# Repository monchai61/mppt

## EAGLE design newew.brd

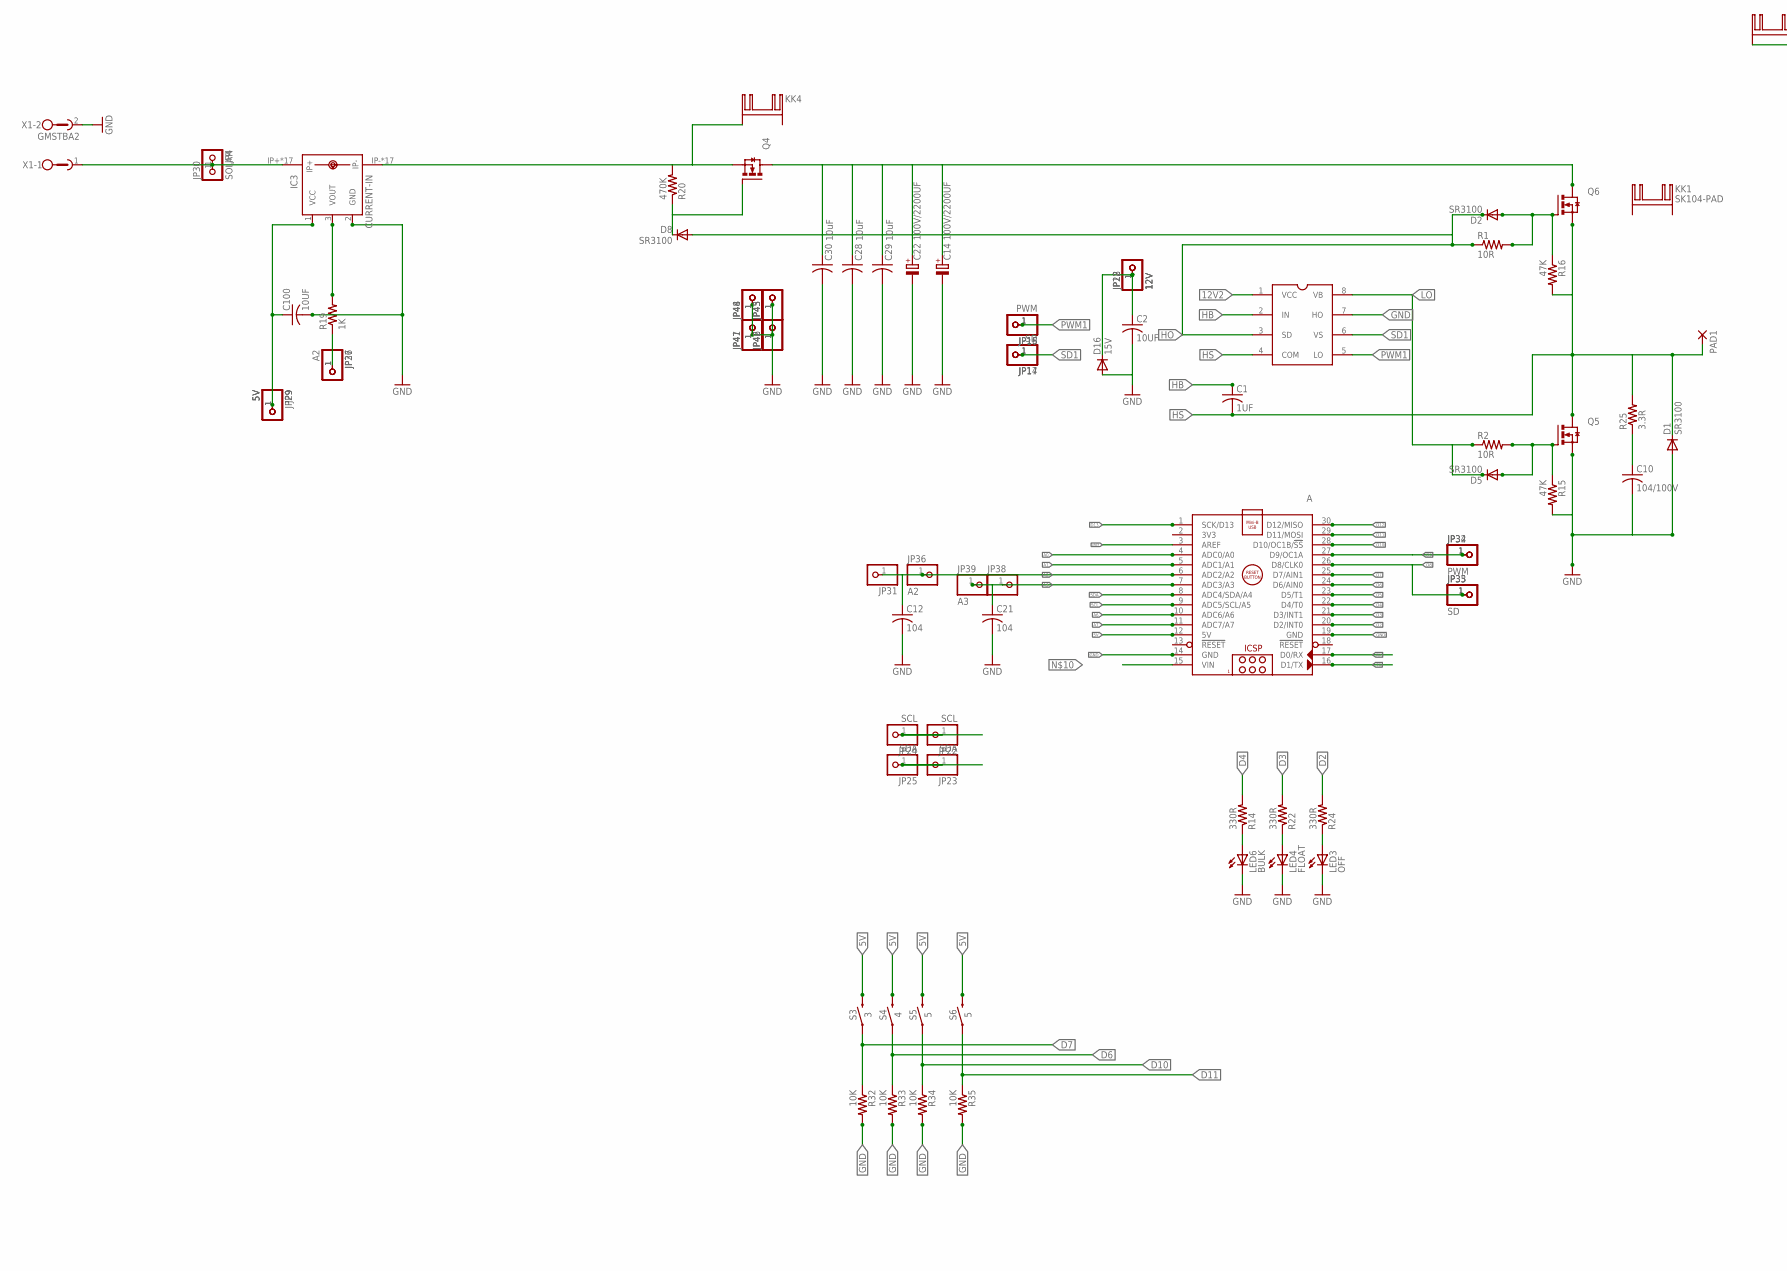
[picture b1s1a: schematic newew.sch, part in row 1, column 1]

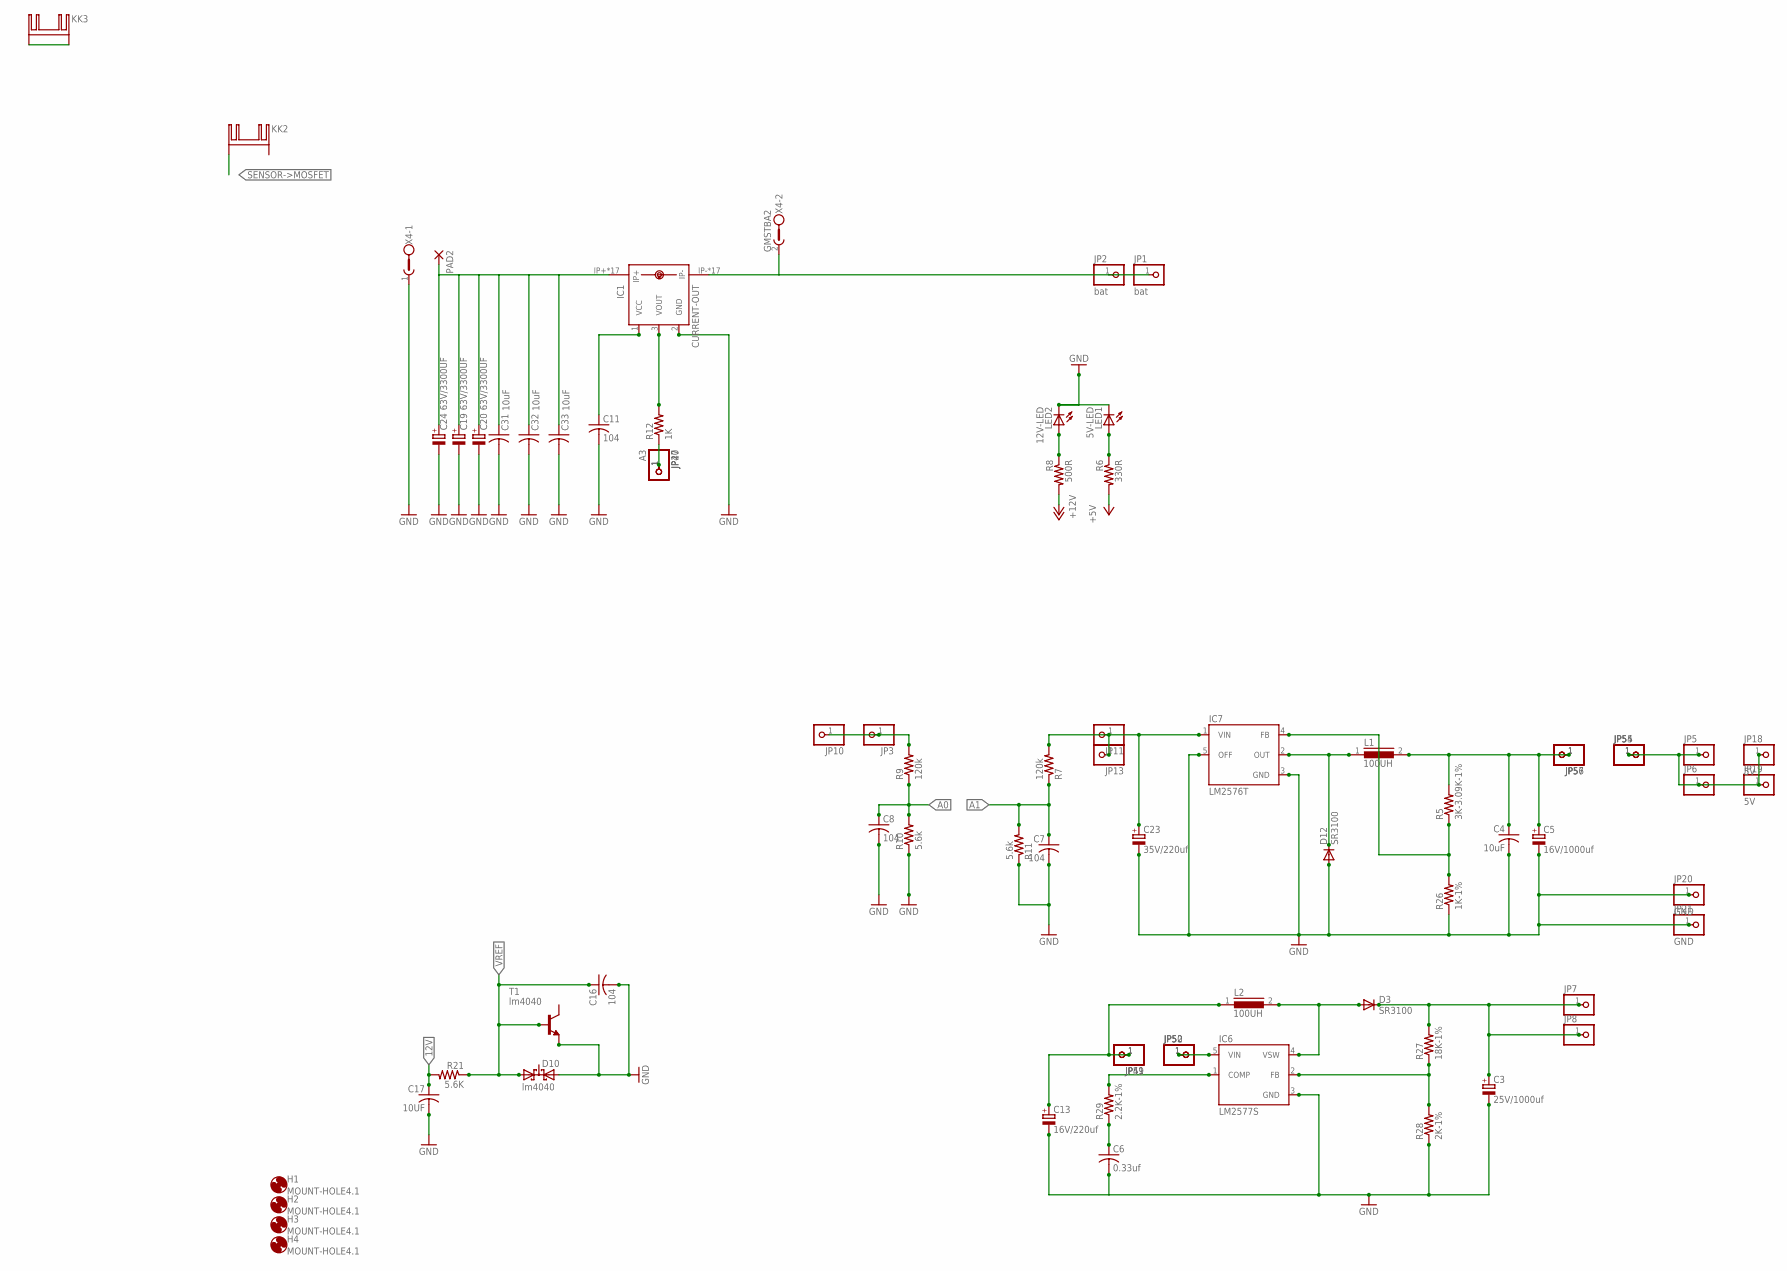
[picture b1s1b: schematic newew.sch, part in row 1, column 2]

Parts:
A: ARDUINO_NANO
C1: 1UF; C025-024X044
C2, C17: 10UF; C025-024X044
C3: 25V/1000uf; E5-8,5
C4: 10uF; C025-024X044
C5: 16V/1000uf; E5-8,5
C6: 0.33uf; C025-024X044
C7, C8, C16: 104; C025-024X044
C10: 104/100V; C075-063X106
C11: 104; C025-025X050
C12, C21: 104; C025-030X050
C13: 16V/220uf; E5-8,5
C14, C22: 100V/2200UF; E7,5-18
C19, C20, C24: 63V/3300UF; E7,5-18
C23: 35V/220uf; E5-8,5
C28, C29, C30, C31, C32, C33: 10uF; C1210K
C100: 10UF; C025-025X050
D1, D3, D12: SR3100; DO27-15
D2, D5, D8: SR3100; DO41-7.6
D10: lm4040; SOT23
D16: 15V; DO41-7.6
H1, H2, H3, H4: MOUNT-HOLE4.1; 4,1
IC1: CURRENT-OUT; CB-PFF
IC3: CURRENT-IN; CB-PFF
IC6: LM2577S; TO263-5
IC7: LM2576T; TO220-5
JP1, JP2: bat; 1X01
JP3, JP4, JP5, JP6, JP7, JP8, JP10, JP11, JP13, JP14, JP15, JP26, JP27, JP31, JP32, JP33, JP38, JP41, JP42, JP43, JP44, JP45, JP46, JP47, JP48, JP49, JP50, JP51, JP52, JP54, JP55, JP56, JP57: PINHD-1X1; 1X01
JP9, JP18, JP19, JP29: 5V; 1X01
JP12, JP28: 12V; 1X01
JP16, JP34: PWM; 1X01
JP17, JP35: SD; 1X01
JP20, JP21: GND; 1X01
JP22, JP24: SCL; 1X01
JP23, JP25: SDA; 1X01
JP30: SOLAR; 1X01
JP36, JP37: A2; 1X01
JP39, JP40: A3; 1X01
KK1, KK2, KK3, KK4: SK104-PAD
L1, L2: 100UH; A26GFC
LED1: 5V-LED; LED3MM
LED2: 12V-LED; LED3MM
LED3: OFF; LED3MM
LED4: FLOAT; LED3MM
LED6: BULK; LED3MM
PAD1, PAD2: 3,81/1,4
Q4, Q5, Q6: IRF3704L-V; TO262-V
R1, R2: 10R; 0204/7
R5: 3K-3.09K-1%; 0204/7
R6, R14, R22, R24: 330R; 0204/7
R7, R9: 120k; 0204/7
R8: 500R; 0204/7
R10, R11: 5.6k; 0204/7
R12, R19: 1K; 0204/7
R15, R16: 47K; 0309/10
R20: 470K; 0309/10
R21: 5.6K; 0204/7
R25: 3.3R; 0309/10
R26: 1K-1%; 0204/7
R27: 18K-1%; 0204/7
R28: 2K-1%; 0204/7
R29: 2.2K-1%; 0204/7
R32, R33, R34, R35: 10K; 0204/7
S3: 3; TACTILE_SWITCH_PTH_6.0MM
S4: 4; TACTILE_SWITCH_PTH_6.0MM
S5, S6: 5; TACTILE_SWITCH_PTH_6.0MM
T1: lm4040; TO92-EBC-OVAL
U$2: MIC4102; IR2104S
X1, X4: GMSTBA2

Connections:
5V: A.12 (5V), C13.+, JP5.1, JP6.1, JP18.1, JP19.1, JP49.1, JP51.1, JP54.1, JP55.1, L2.1, R6.2, S3.3 (2), S4.3 (2), S5.3 (2), S6.3 (2)
5V2: C11.1, C100.1, IC1.1 (VCC), IC3.1 (VCC), JP9.1, JP29.1
12V: C3.+, C17.1, D3.C, JP7.1, JP8.1, R8.2, R21.2, R27.2
12V2: C2.1, D16.C, JP12.1, JP28.1, U$2.1 (VCC)
A0: A.4 (ADC0/A0), C8.1, R9.1, R10.2
A1: A.5 (ADC1/A1), C7.1, R7.1, R11.2
A2: A.6 (ADC2/A2), C12.1, JP31.1, JP36.1
A3: A.7 (ADC3/A3), C21.1, JP38.1, JP39.1
A6: A.10 (ADC6/A6)
A7: A.11 (ADC7/A7)
ASDA: C4.1, C5.+, JP56.1, JP57.1, L1.2, R5.2
D2: A.20 (D2/INT0), R24.2
D3: A.21 (D3/INT1), R22.2
D4: A.22 (D4/T0), R14.2
D5: A.23 (D5/T1)
D6: A.24 (D6/AIN0), R33.1, S4.1
D7: A.25 (D7/AIN1), R32.1, S3.1
D8: A.26 (D8/CLK0), JP33.1, JP35.1
D9: A.27 (D9/OC1A), JP32.1, JP34.1
D10: A.28 (D10/OC1B/!SS), R34.1, S5.1
D11: A.29 (D11/MOSI), R35.1, S6.1
D12: A.30 (D12/MISO)
D13: A.1 (SCK/D13)
EW: JP3.1, JP10.1, R9.2
GND: A.14 (GND), A.19 (GND), C2.2, C3.-, C4.2, C5.-, C6.2, C7.2, C8.2, C10.2, C11.2, C12.2, C13.-, C14.-, C16.2, C17.2, C19.-, C20.-, C21.2, C22.-, C23.-, C24.-, C28.2, C29.2, C30.2, C31.2, C32.2, C33.2, C100.2, D1.A, D10.2 (A2), D12.A, D16.A, IC1.2 (GND), IC3.2 (GND), IC6.3 (GND), IC7.3 (GND), IC7.5 (OFF), JP20.1, JP21.1, JP41.1, JP42.1, JP43.1, JP44.1, JP45.1, JP46.1, JP47.1, JP48.1, LED1.K (C), LED2.K (C), LED3.K (C), LED4.K (C), LED6.K (C), Q5.3 (S), R10.1, R11.1, R15.2, R26.1, R28.1, R32.2, R33.2, R34.2, R35.2, T1.E, U$2.7 (HO), X1.2, X4.1
HB: C1.1, U$2.2 (IN)
HO: D2.C, D8.A, R1.1, U$2.3 (SD)
HS: C1.2, D1.C, KK3.K1, KK3.K2, PAD1.1, Q5.2 (D), Q6.3 (S), R16.2, R25.2, U$2.4 (COM)
INDUCTOR->SENSOR: C19.+, C20.+, C24.+, C31.1, C32.1, C33.1, IC1.IP+, IC1.IP+@2 (IP+), IC1.IP+@3 (IP+), IC1.IP+@4 (IP+), IC1.IP+@5 (IP+), IC1.IP+@6 (IP+), IC1.IP+@7 (IP+), IC1.IP+@8 (IP+), IC1.IP+@9 (IP+), IC1.IP+@10 (IP+), IC1.IP+@11 (IP+), IC1.IP+@12 (IP+), IC1.IP+@13 (IP+), IC1.IP+@14 (IP+), IC1.IP+@15 (IP+), IC1.IP+@16 (IP+), IC1.IP+@17 (IP+), PAD2.1
LO: D5.C, R2.1, U$2.8 (VB)
unnamed: LED6.A, R14.1
unnamed: D12.C, IC7.2 (OUT), L1.1
unnamed: LED4.A, R22.1
unnamed: D2.A, Q6.1 (G), R1.2, R16.1
unnamed: C10.1, R25.1
unnamed: LED3.A, R24.1
unnamed: IC3.IP-, IC3.IP-@2 (IP-), IC3.IP-@3 (IP-), IC3.IP-@4 (IP-), IC3.IP-@5 (IP-), IC3.IP-@6 (IP-), IC3.IP-@7 (IP-), IC3.IP-@8 (IP-), IC3.IP-@9 (IP-), IC3.IP-@10 (IP-), IC3.IP-@11 (IP-), IC3.IP-@12 (IP-), IC3.IP-@13 (IP-), IC3.IP-@14 (IP-), IC3.IP-@15 (IP-), IC3.IP-@16 (IP-), IC3.IP-@17 (IP-), KK4.K1, Q4.3 (S), R20.2
unnamed: LED1.A, R6.1
unnamed: IC1.3 (VOUT), R12.2
unnamed: IC1.IP-, IC1.IP-@2 (IP-), IC1.IP-@3 (IP-), IC1.IP-@4 (IP-), IC1.IP-@5 (IP-), IC1.IP-@6 (IP-), IC1.IP-@7 (IP-), IC1.IP-@8 (IP-), IC1.IP-@9 (IP-), IC1.IP-@10 (IP-), IC1.IP-@11 (IP-), IC1.IP-@12 (IP-), IC1.IP-@13 (IP-), IC1.IP-@14 (IP-), IC1.IP-@15 (IP-), IC1.IP-@16 (IP-), IC1.IP-@17 (IP-), JP1.1, JP2.1, X4.2
unnamed: LED2.A, R8.1
unnamed: IC3.3 (VOUT), R19.2
unnamed: IC6.5 (VIN), JP50.1, JP52.1
unnamed: D8.C, Q4.1 (G), R20.1
unnamed: D5.A, Q5.1 (G), R2.2, R15.1
unnamed: JP26.1, JP37.1, R19.1
unnamed: C23.+, IC7.1 (VIN), JP11.1, JP13.1, R7.2
unnamed: IC7.4 (FB), R5.1, R26.2
unnamed: D3.A, IC6.4 (VSW), L2.2
unnamed: IC6.2 (FB), R27.1, R28.2
unnamed: C6.1, R29.1
unnamed: IC6.1 (COMP), R29.2
PWM1: JP15.1, JP16.1, U$2.5 (LO)
RX: A.17 (D0/RX)
SCL: A.9 (ADC5/SCL/A5), JP22.1, JP24.1
SD1: JP14.1, JP17.1, U$2.6 (VS)
SDA: A.8 (ADC4/SDA/A4), JP23.1, JP25.1
SDS: JP27.1, JP40.1, R12.1
SENSOR->MOSFET: C14.+, C22.+, C28.1, C29.1, C30.1, KK2.K1, Q4.2 (D), Q6.2 (D)
SOLAR-POSITIVE-BUS: IC3.IP+, IC3.IP+@2 (IP+), IC3.IP+@3 (IP+), IC3.IP+@4 (IP+), IC3.IP+@5 (IP+), IC3.IP+@6 (IP+), IC3.IP+@7 (IP+), IC3.IP+@8 (IP+), IC3.IP+@9 (IP+), IC3.IP+@10 (IP+), IC3.IP+@11 (IP+), IC3.IP+@12 (IP+), IC3.IP+@13 (IP+), IC3.IP+@14 (IP+), IC3.IP+@15 (IP+), IC3.IP+@16 (IP+), IC3.IP+@17 (IP+), JP4.1, JP30.1, X1.1
TX: A.16 (D1/TX)
VREF: A.3 (AREF), C16.1, D10.1 (A1), R21.1, T1.B

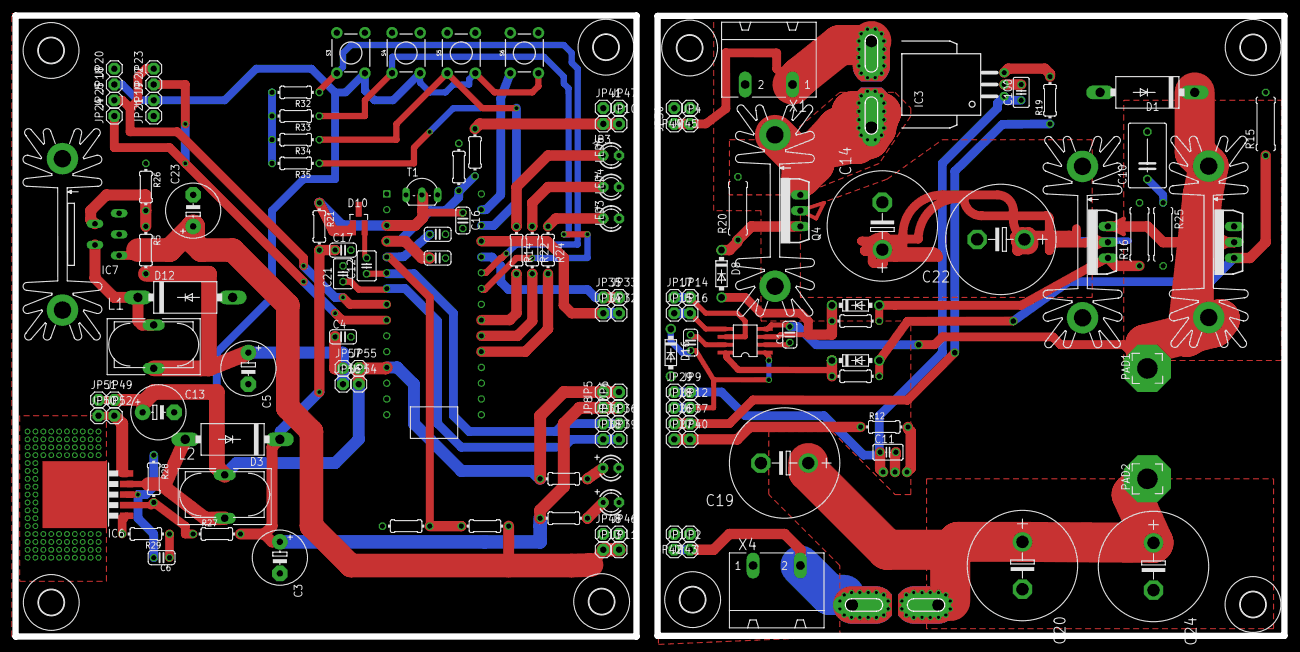
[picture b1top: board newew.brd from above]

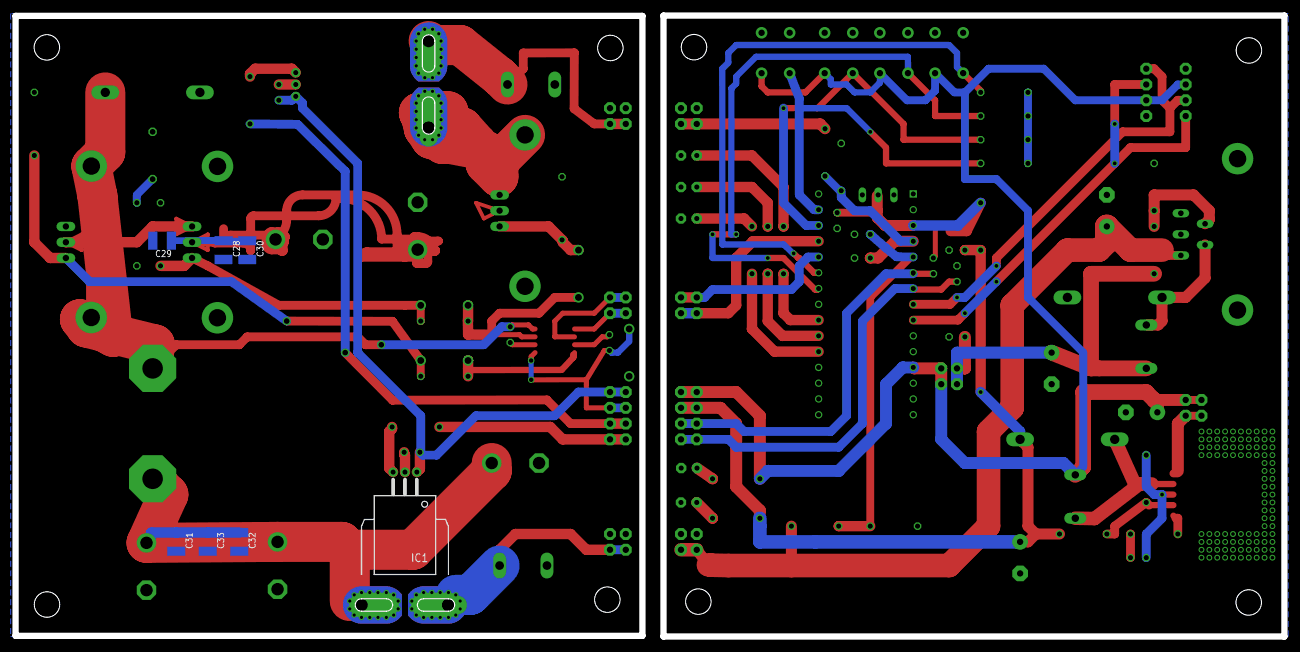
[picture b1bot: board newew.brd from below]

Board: 2 copper layers, 204.3 x 100.0 mm, 156 parts (7 on the bottom side), 55 nets.

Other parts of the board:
H5, H7, H8, H9: MOUNT-HOLE4.1; 4,1

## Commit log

2018-08-01 SCHEMATIC AND PCB

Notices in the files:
parts and their libraries:
SparkFun-Switches: Licensing: Creative Commons ShareAlike 4.0 International - https://creativecommons.org/licenses/by-sa/4.0
